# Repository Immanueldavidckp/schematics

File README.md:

# MEWP Telematics Tracker — hardware

CAN-connected GPS/LTE tracker for rental MEWPs (boom/scissor lifts).
Powered from machine batteries with internal Li-ion backup, 2 isolated digital
inputs, 2 low-side outputs, ignition sense, 6-axis IMU, and ≥6 days of local
telemetry buffering.

**Status: milestone 3 complete.** Schematics are drawn and ERC-clean.
Layout has not started and is gated on the open flags below.

| | |
|---|---|
| Target | India · ~₹2,000/unit ex-works at ≥500 pcs · 5-year field life |
| Fab/assembly | JLCPCB (prototypes), Indian EMS later |
| EDA | KiCad 10 |
| Input range | 10.5–100 V DC (80 V packs reach ~96–100 V while charging) |

## Design

| Ref | Part | Function |
|---|---|---|
| U1 | Quectel EC200U-CN | LTE Cat-1 bis + GNSS |
| U2 | Artery AT32F403ACGT7 | MCU, M4 240 MHz, LQFP-48 |
| U3 | QST QMI8658B | 6-axis IMU |
| U4 | SIT1051AT/3 | CAN-FD transceiver |
| U5 | EG Micro EG11752 | 200 V abs-max buck → 5V0 |
| U6 | TI BQ25606 | 1S charger + power path |
| U7 | GD25Q64ESIGR | 8 MB SPI NOR telemetry buffer |
| U8 | TI TXB0104 | 1.8 V ↔ 3.3 V level shift |
| U9 | ME6211C33M5G | 3V3 LDO |

## Layout

```
telematics-tracker.kicad_pro/.kicad_sch/.kicad_pcb   project + root sheet
mcu / storage / io / modem_rf / power .kicad_sch     hierarchical sheets
lib/jlc.kicad_sym, lib/jlc.pretty, lib/jlc.3dshapes  LCSC parts (easyeda2kicad)
tools/schgen.py                                      KiCad S-expression emitter
tools/sheets.py                                      the schematics, as code
tools/checkpins.py                                   netlist-vs-spec guard
docs/                                                see below
erc-*.rpt                                            ERC evidence
```

Sheets are **generated**, not hand-drawn: edit `tools/sheets.py` and run
`python tools/sheets.py`, which rewrites all five sheets plus the root.
Symbol definitions are embedded in each sheet, so they parse without library
resolution. UUIDs are deterministic, so regeneration is diffable.

## Verification

Every change is gated on three checks:

```bash
python tools/sheets.py                                    # regenerate
kicad-cli sch erc  --output erc-full.rpt telematics-tracker.kicad_sch
kicad-cli sch export netlist --format kicadsexpr --output nl.net telematics-tracker.kicad_sch
python tools/checkpins.py nl.net                          # exits non-zero on any mismatch
```

Current: **ERC 0 errors** (14 warnings, each justified in the design log) ·
**48/48** handoff §5 pin-map rows verified against the netlist with far-end
checks · **8/8** DO default-OFF structural assertions.

The netlist guard exists because ERC does not catch everything. It has caught
four real faults that ERC reported only as warnings or not at all: a shorted-out
gate resistor, CANL tied to GND by overlapping stubs, VBAT merged into 3V3, and
a root-sheet wrap-around that shorted three rails.

## Documentation

| File | Contents |
|---|---|
| [design-log.md](design-log.md) | Every decision, deviation and flag, with evidence. Start here. |
| [docs/telematics-handoff.md](docs/telematics-handoff.md) | The governing spec (BOM, pin map, design rules) |
| [docs/f9-review.md](docs/f9-review.md) | EC200U pin-map review table — **sign-off gate** |
| [docs/ec200u-pinmap-extracted.md](docs/ec200u-pinmap-extracted.md) | All 144 pins, VERIFIED / NEEDS-HUMAN |
| [docs/section5-checklist.txt](docs/section5-checklist.txt) | Generated pin-map verification output |
| [docs/firmware-notes.md](docs/firmware-notes.md) | Hardware facts firmware must honour (FW-1…17, BV-1…4) |
| [docs/placement-study.svg](docs/placement-study.svg) | Milestone-4 placement study (provisional outline) |
| [docs/SKILL.md](docs/SKILL.md) | KiCad workflow rules for this project |

## Open flags (blocking layout)

- **F-9** — EC200U symbol came from an EasyEDA entry built around the MobileTek
  L610; its pin numbering contradicts Quectel Table 7 (VBAT_BB 90/91 vs 59/60).
  Only VERIFIED pins are wired; **76 pins are deliberately no-connect**, incl.
  35 probable GND pins. Human sign-off on `docs/f9-review.md` is required before
  layout.
- **F-15** — R80 10 Ω has no load-line solution at the 10.5 V floor at full
  load. Recommend 1 Ω anti-surge (C55348540).
- **F-13** modem bulk caps are X5R 6.3 V on a 4.35 V rail (violates the
  2:1 / X7R rule) · **F-14** six missing test points · **F-12** EG11752 R_IS and
  min-on-time bench items · **F-16** SIM holder locating posts · **F-17** MFF2
  land pattern · **F-5** provisional passive C-numbers.

Nothing here has been fabricated. Re-verify every LCSC C-number on order day.

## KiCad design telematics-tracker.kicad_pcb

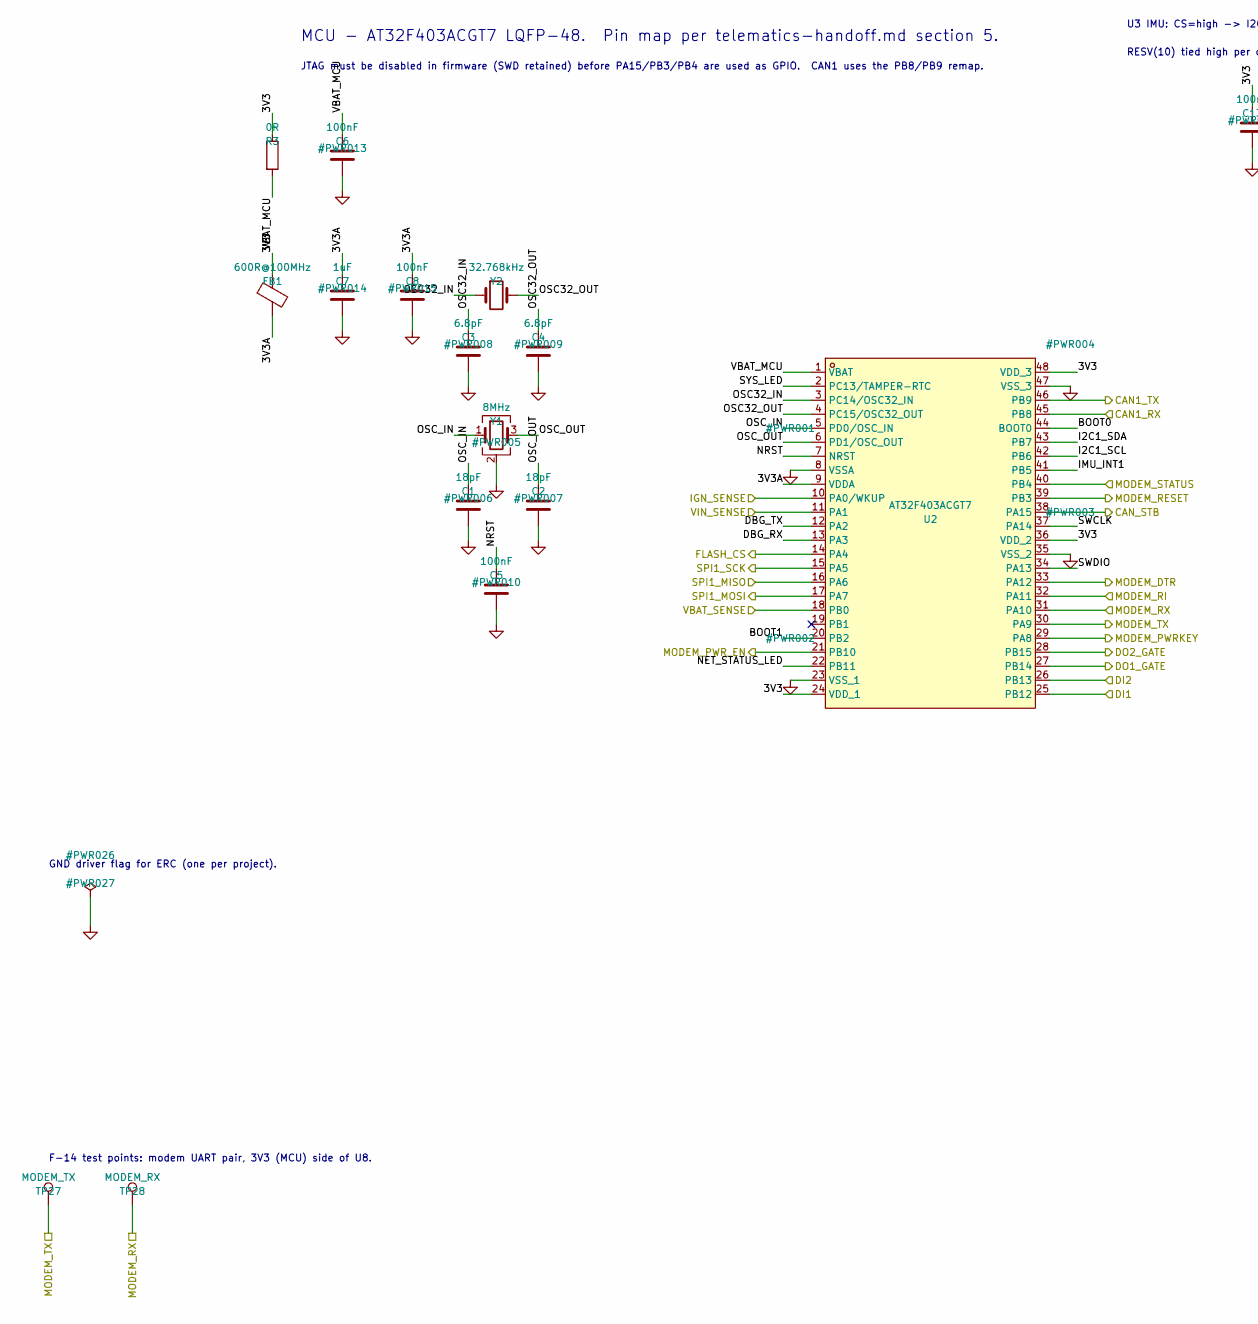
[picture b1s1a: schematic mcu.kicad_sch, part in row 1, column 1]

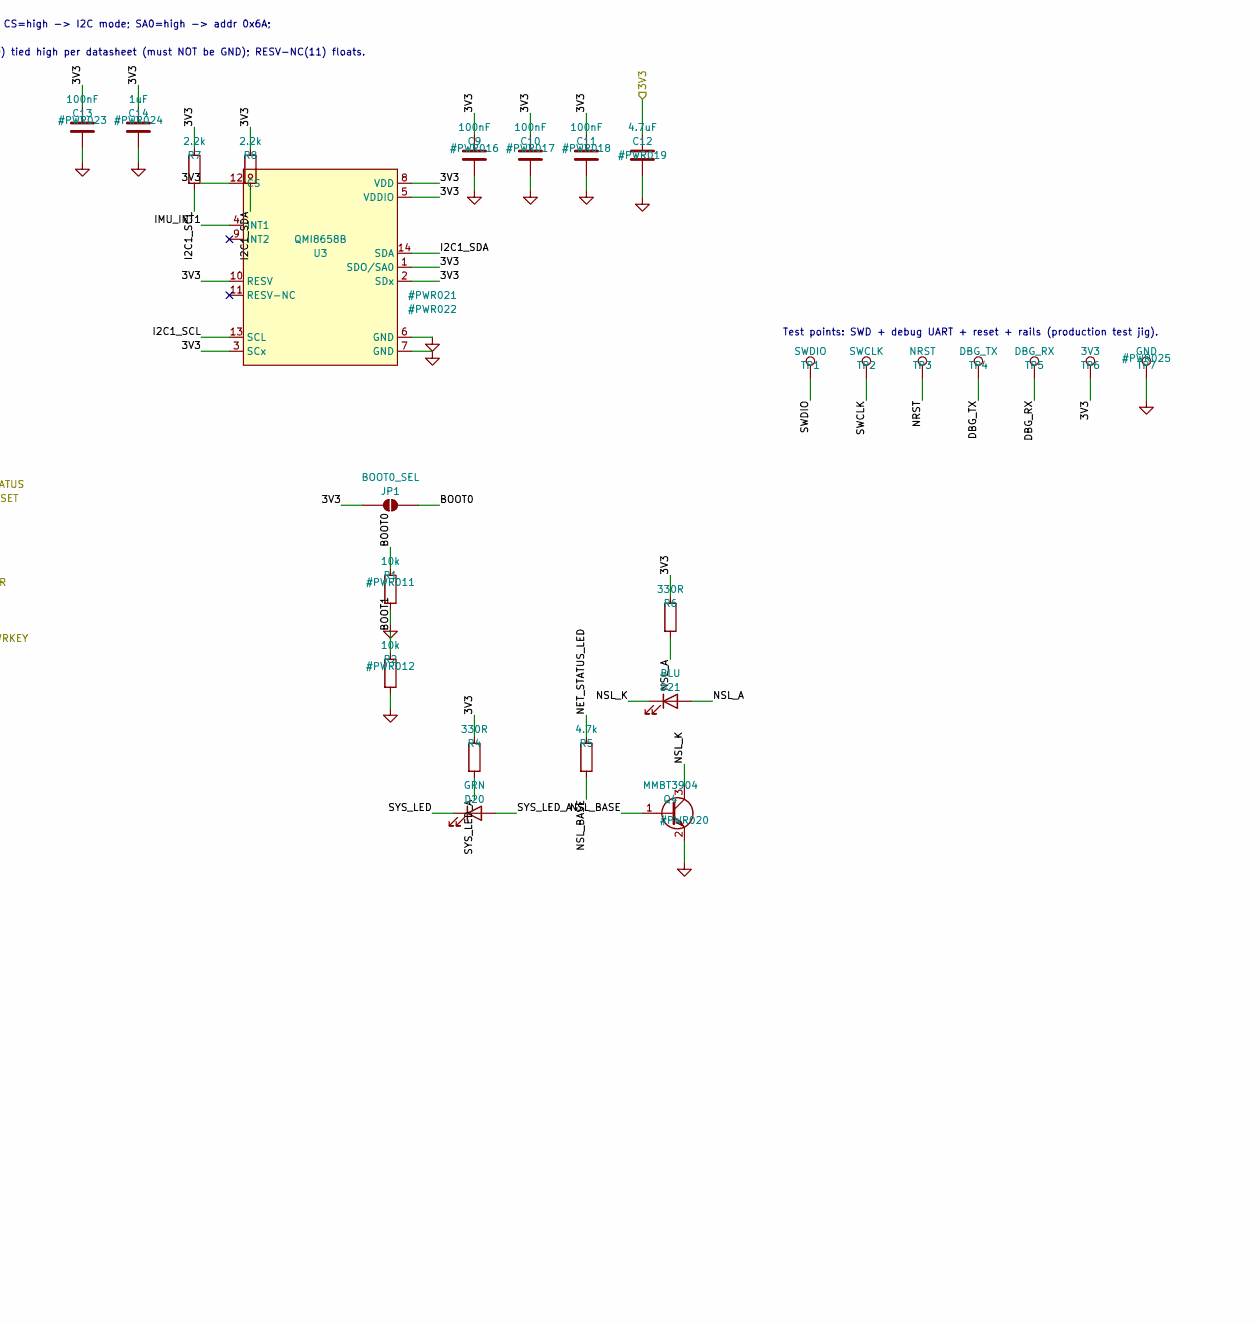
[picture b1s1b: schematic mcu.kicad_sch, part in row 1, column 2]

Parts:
C1, C2: 18pF; C_0603_1608Metric; LCSC C1647
C3, C4: 6.8pF; C_0603_1608Metric; LCSC C318672
C5, C6, C8, C9, C10, C11, C13: 100nF; C_0603_1608Metric; LCSC C14663
C7, C14: 1uF; C_0603_1608Metric; LCSC C106858
C12: 4.7uF; C_0805_2012Metric; LCSC C354262
D20: GRN; LED_0603_1608Metric; LCSC C12624
D21: BLU; LED_0603_1608Metric; LCSC C2288
FB1: 600R@100MHz; L_0805_2012Metric; LCSC C1017
JP1: BOOT0_SEL; SolderJumper-2_P1.3mm_Open_Pad1.0x1.5mm
Q4: MMBT3904; SOT-23; LCSC C20526
R1, R2: 10k; R_0805_2012Metric; LCSC C17414
R3: 0R; R_0805_2012Metric; LCSC C17477
R4, R6: 330R; R_0805_2012Metric; LCSC C17630
R5: 4.7k; R_0805_2012Metric; LCSC C17673
R7, R8: 2.2k; R_0805_2012Metric; LCSC C17520
TP1: SWDIO; TestPoint_Pad_D1.5mm
TP2: SWCLK; TestPoint_Pad_D1.5mm
TP3: NRST; TestPoint_Pad_D1.5mm
TP4: DBG_TX; TestPoint_Pad_D1.5mm
TP5: DBG_RX; TestPoint_Pad_D1.5mm
TP6: 3V3; TestPoint_Pad_D1.5mm
TP7: GND; TestPoint_Pad_D1.5mm
TP27: MODEM_TX; TestPoint_Pad_D1.5mm
TP28: MODEM_RX; TestPoint_Pad_D1.5mm
U2: AT32F403ACGT7; LQFP-48_L7.0-W7.0-P0.50-LS9.0-BL_1; LCSC C55058656
U3: QMI8658B; LGA-14_L3.0-W2.5-P0.50-TL; LCSC C5380158
Y1: 8MHz; Crystal_SMD_3225-4Pin_3.2x2.5mm; LCSC C2682775
Y2: 32.768kHz; Crystal_SMD_3215-2Pin_3.2x1.5mm; LCSC C48615

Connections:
3V3: C9.1, C10.1, C11.1, C12.1, C13.1, C14.1, FB1.1, JP1.1 (A), R3.1, R4.1, R6.1, R7.1, R8.1, TP6.1, U2.24 (VDD_1), U2.36 (VDD_2), U2.48 (VDD_3), U3.1 (SDO/SA0), U3.2 (SDx), U3.3 (SCx), U3.5 (VDDIO), U3.8 (VDD), U3.10 (RESV), U3.12 (CS); also elsewhere on the board
/mcu/3V3A: C7.1, C8.1, FB1.2, U2.9 (VDDA)
/mcu/BOOT0: JP1.2 (B), R1.1, U2.44 (BOOT0)
/mcu/BOOT1: R2.1, U2.20 (PB2)
/mcu/DBG_RX: TP5.1, U2.13 (PA3)
/mcu/DBG_TX: TP4.1, U2.12 (PA2)
/mcu/I2C1_SCL: R7.2, U2.42 (PB6), U3.13 (SCL)
/mcu/I2C1_SDA: R8.2, U2.43 (PB7), U3.14 (SDA)
/mcu/IMU_INT1: U2.41 (PB5), U3.4 (INT1)
/mcu/NET_STATUS_LED: R5.1, U2.22 (PB11)
/mcu/NRST: C5.1, TP3.1, U2.7 (NRST)
/mcu/NSL_A: D21.2 (A), R6.2
/mcu/NSL_BASE: Q4.1 (B), R5.2
/mcu/NSL_K: D21.1 (K), Q4.3 (C)
/mcu/OSC32_IN: C3.1, U2.3 (PC14/OSC32_IN), Y2.1
/mcu/OSC32_OUT: C4.1, U2.4 (PC15/OSC32_OUT), Y2.2
/mcu/OSC_IN: C1.1, U2.5 (PD0/OSC_IN), Y1.1
/mcu/OSC_OUT: C2.1, U2.6 (PD1/OSC_OUT), Y1.3
/mcu/SWCLK: TP2.1, U2.37 (PA14)
/mcu/SWDIO: TP1.1, U2.34 (PA13)
/mcu/SYS_LED: D20.1 (K), U2.2 (PC13/TAMPER-RTC)
/mcu/SYS_LED_A: D20.2 (A), R4.2
/mcu/VBAT_MCU: C6.1, R3.2, U2.1 (VBAT)
CAN1_RX: U2.45 (PB8); also elsewhere on the board
CAN1_TX: U2.46 (PB9); also elsewhere on the board
CAN_STB: U2.38 (PA15); also elsewhere on the board
DI1: U2.25 (PB12); also elsewhere on the board
DI2: U2.26 (PB13); also elsewhere on the board
DO1_GATE: U2.27 (PB14); also elsewhere on the board
DO2_GATE: U2.28 (PB15); also elsewhere on the board
FLASH_CS: U2.14 (PA4); also elsewhere on the board
GND: C1.2, C2.2, C3.2, C4.2, C5.2, C6.2, C7.2, C8.2, C9.2, C10.2, C11.2, C12.2, C13.2, C14.2, Q4.2 (E), R1.2, R2.2, TP7.1, U2.8 (VSSA), U2.23 (VSS_1), U2.35 (VSS_2), U2.47 (VSS_3), U3.6 (GND), U3.7 (GND), Y1.2 (G), Y1.4 (G); also elsewhere on the board
IGN_SENSE: U2.10 (PA0/WKUP)
MODEM_DTR: U2.33 (PA12); also elsewhere on the board
MODEM_PWRKEY: U2.29 (PA8); also elsewhere on the board
MODEM_PWR_EN: U2.21 (PB10); also elsewhere on the board
MODEM_RESET: U2.39 (PB3); also elsewhere on the board
MODEM_RI: U2.32 (PA11); also elsewhere on the board
MODEM_RX: TP28.1, U2.31 (PA10); also elsewhere on the board
MODEM_STATUS: U2.40 (PB4); also elsewhere on the board
MODEM_TX: TP27.1, U2.30 (PA9); also elsewhere on the board
SPI1_MISO: U2.16 (PA6); also elsewhere on the board
SPI1_MOSI: U2.17 (PA7); also elsewhere on the board
SPI1_SCK: U2.15 (PA5); also elsewhere on the board
VBAT_SENSE: U2.18 (PB0)
VIN_SENSE: U2.11 (PA1)

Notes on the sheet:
MCU - AT32F403ACGT7 LQFP-48. Pin map per telematics-handoff.md section 5.
JTAG must be disabled in firmware (SWD retained) before PA15/PB3/PB4 are used as GPIO. CAN1 uses the PB8/PB9 remap.
U3 IMU: CS=high -> I2C mode; SA0=high -> addr 0x6A;
RESV(10) tied high per datasheet (must NOT be GND); RESV-NC(11) floats.
Test points: SWD + debug UART + reset + rails (production test jig).
F-14 test points: modem UART pair, 3V3 (MCU) side of U8.
GND driver flag for ERC (one per project).

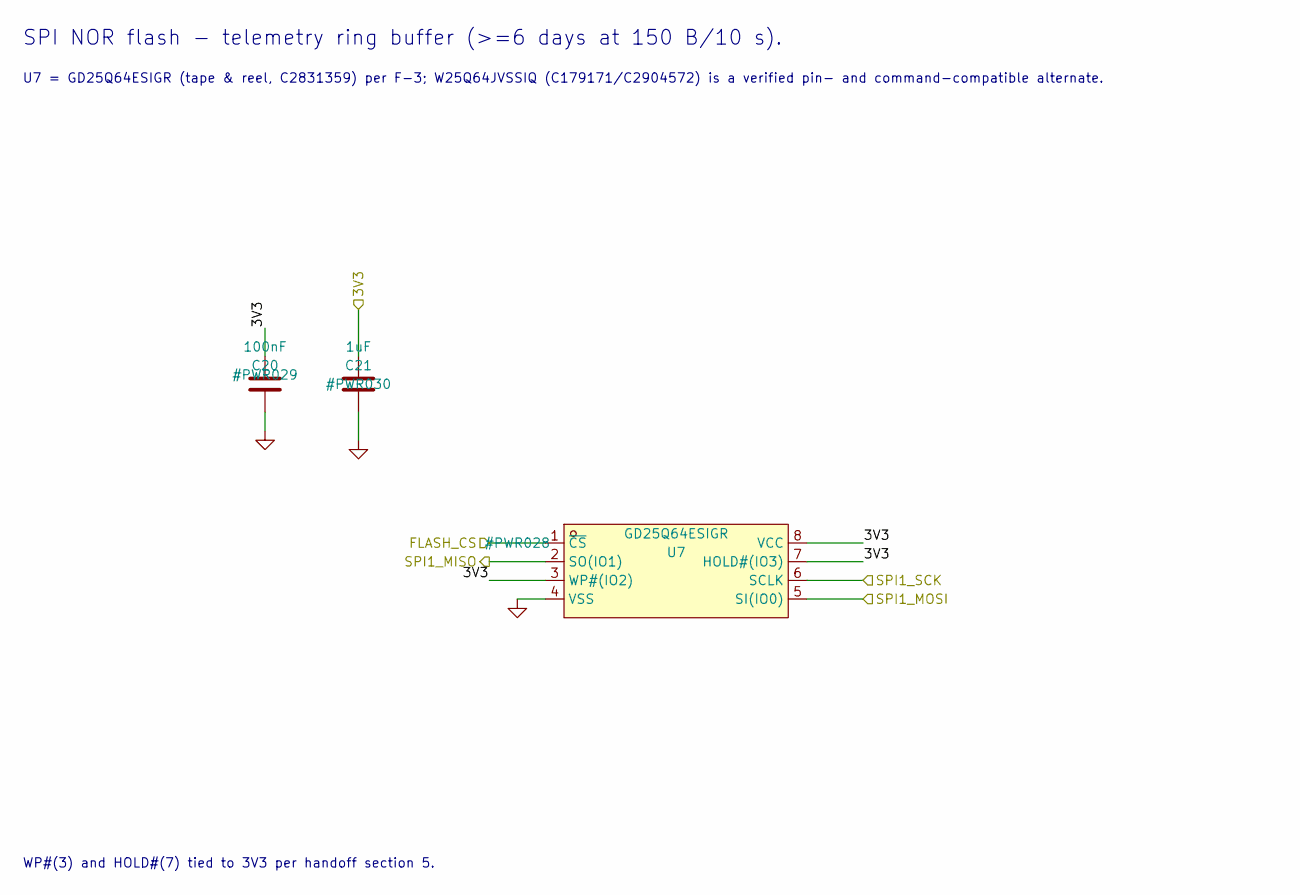
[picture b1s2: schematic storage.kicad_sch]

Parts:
C20: 100nF; C_0603_1608Metric; LCSC C14663
C21: 1uF; C_0603_1608Metric; LCSC C106858
U7: GD25Q64ESIGR; SOP-8_L5.3-W5.3-P1.27-LS8.0-BL; LCSC C2831359

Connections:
3V3: C20.1, C21.1, U7.3 (WP#(IO2)), U7.7 (HOLD#(IO3)), U7.8 (VCC); also elsewhere on the board
FLASH_CS: U7.1 (~CS); also elsewhere on the board
GND: C20.2, C21.2, U7.4 (VSS); also elsewhere on the board
SPI1_MISO: U7.2 (SO(IO1)); also elsewhere on the board
SPI1_MOSI: U7.5 (SI(IO0)); also elsewhere on the board
SPI1_SCK: U7.6 (SCLK); also elsewhere on the board

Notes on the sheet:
SPI NOR flash - telemetry ring buffer (>=6 days at 150 B/10 s).
U7 = GD25Q64ESIGR (tape & reel, C2831359) per F-3; W25Q64JVSSIQ (C179171/C2904572) is a verified pin- and command-compatible alternate.
WP#(3) and HOLD#(7) tied to 3V3 per handoff section 5.

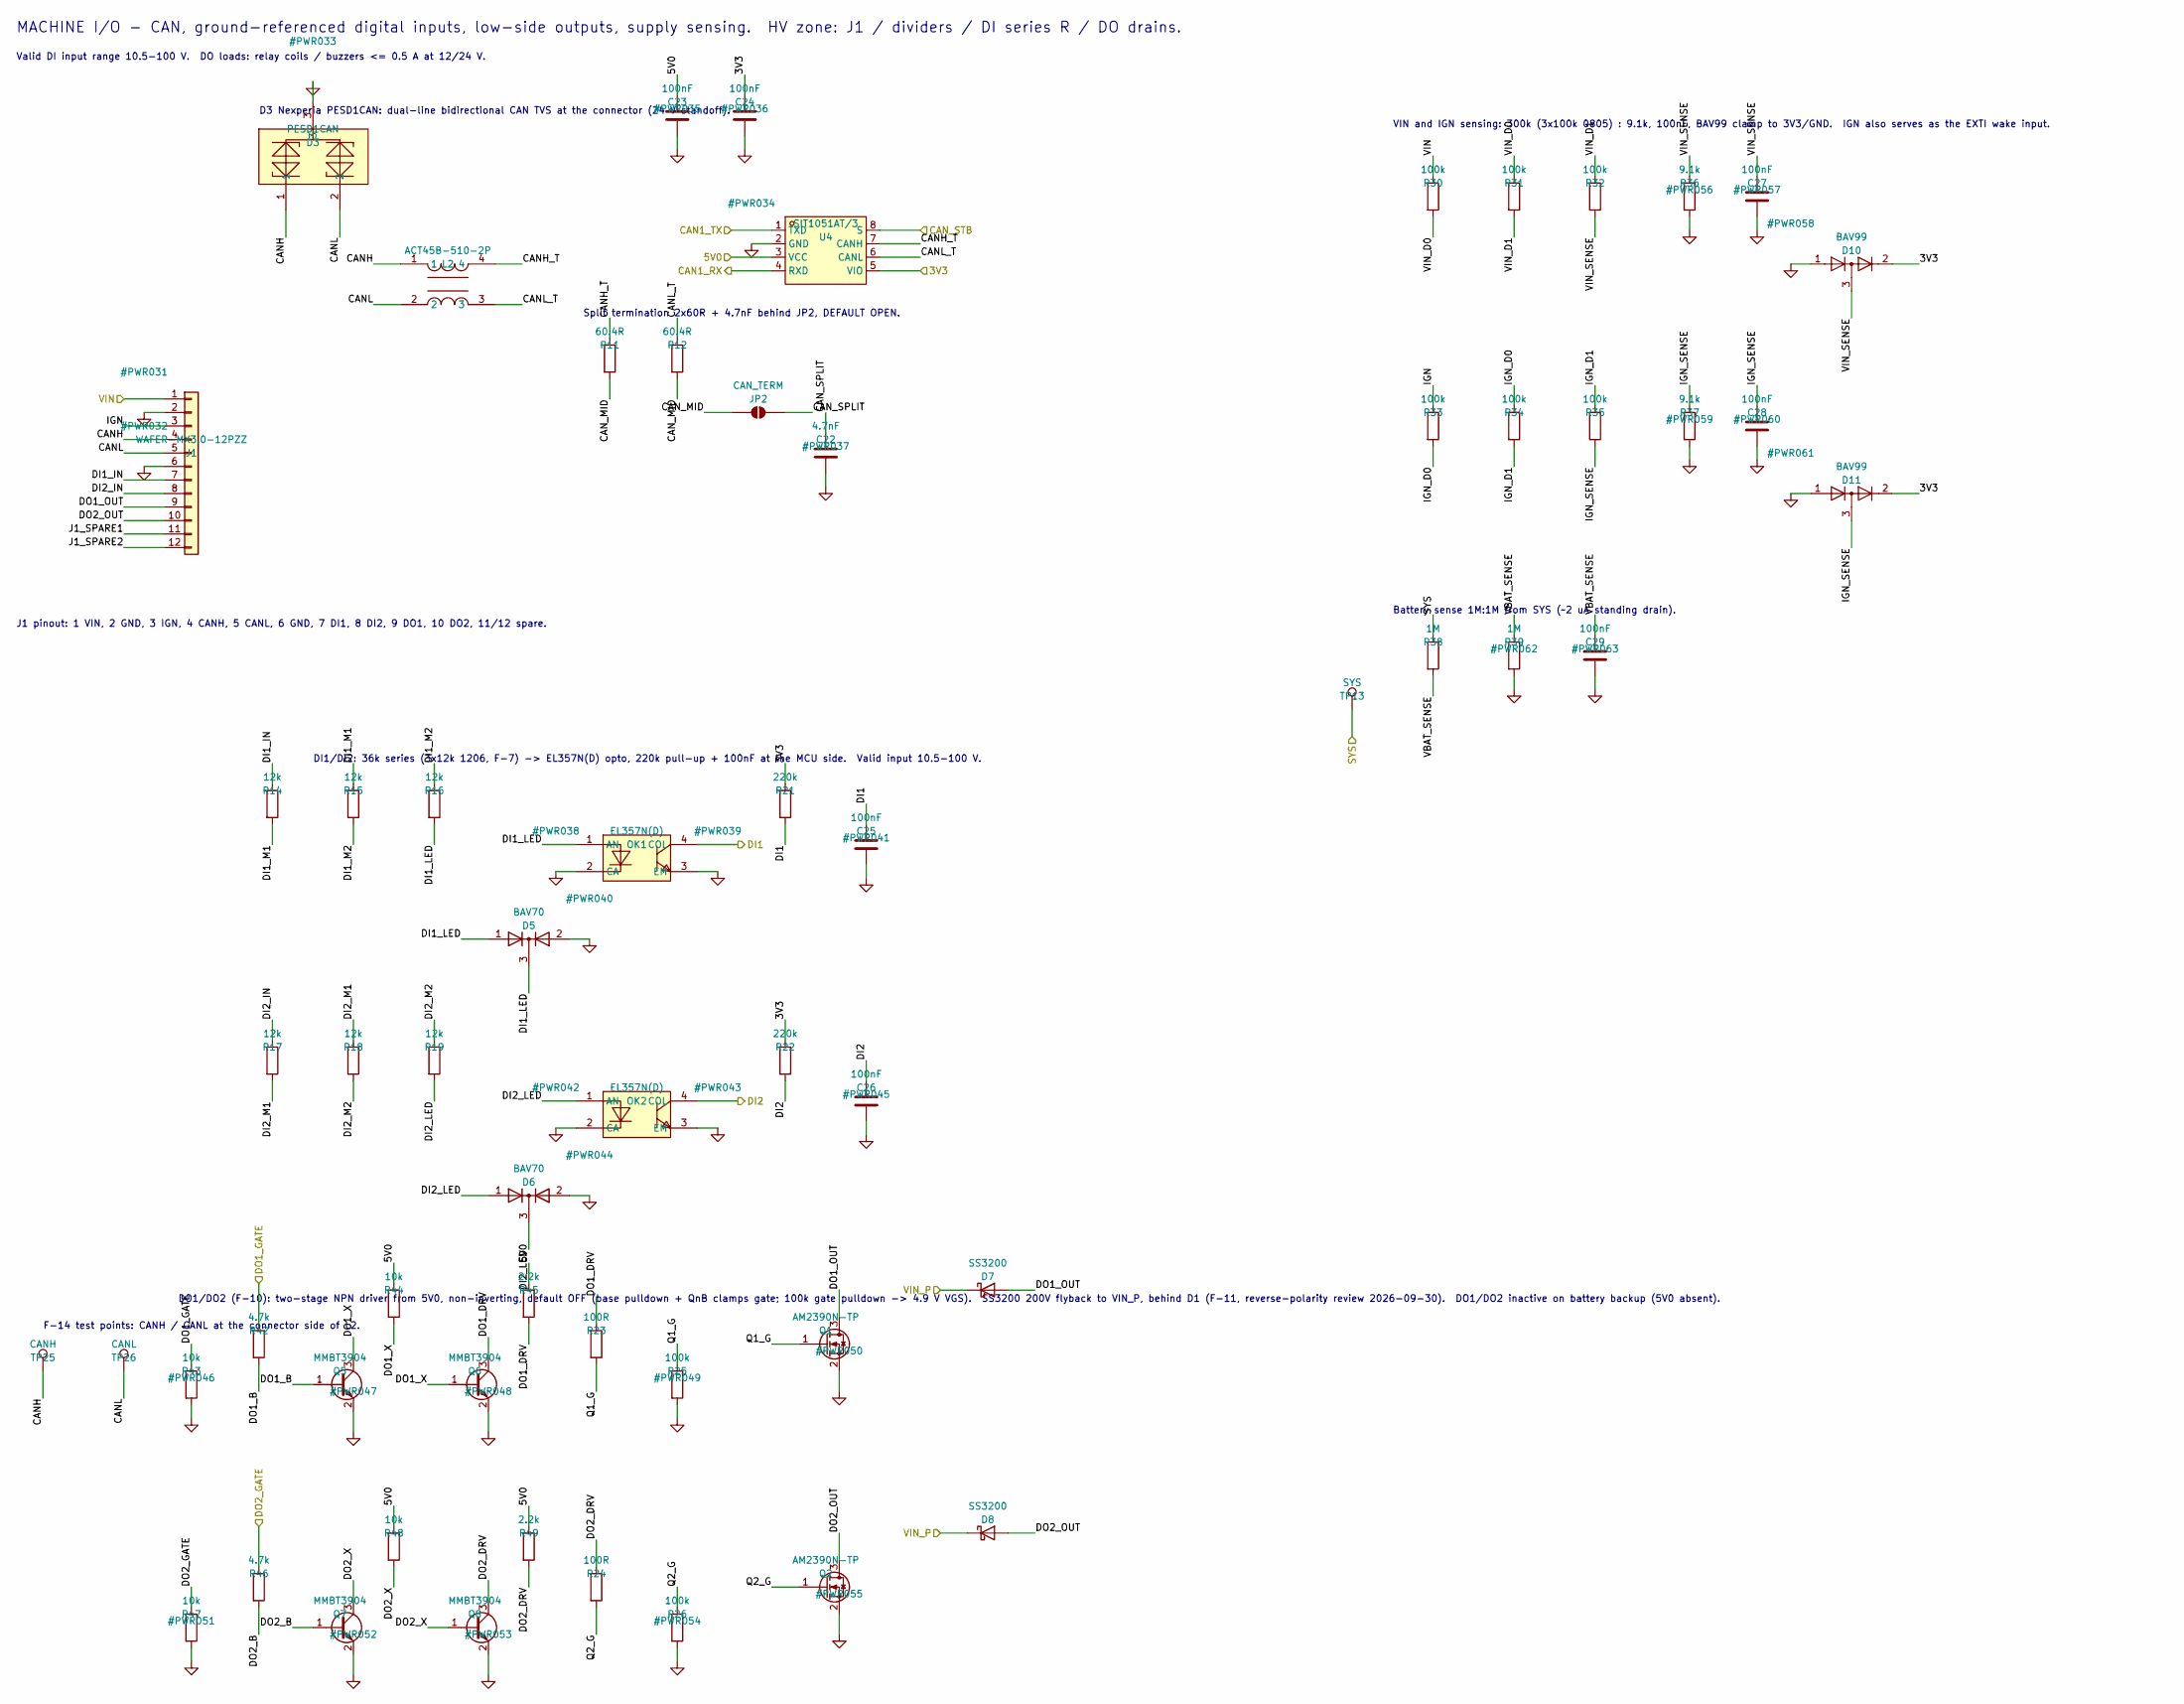
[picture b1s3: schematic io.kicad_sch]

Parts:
C22: 4.7nF; C_0603_1608Metric; LCSC C1621
C23, C24, C25, C26, C27, C28, C29: 100nF; C_0603_1608Metric; LCSC C14663
D3: PESD1CAN; SOT-23_L2.9-W1.3-P1.90-LS2.4-BR; LCSC C15771
D5, D6: BAV70; SOT-23; LCSC C2501
D7, D8: SS3200; D_SMA; LCSC C65001
D10, D11: BAV99; SOT-23; LCSC C2500
J1: WAFER-MX3.0-12PZZ; XUNPU_MX3.0-12PZZ_2x06_P3.00mm_Vertical; LCSC C7588012
JP2: CAN_TERM; SolderJumper-2_P1.3mm_Open_Pad1.0x1.5mm
L2: ACT45B-510-2P; IND-SMD_4P-L4.5-W3.2-TL; LCSC C76584
OK1, OK2: EL357N(D); OPTO-SMD-4_L4.4-W4.1-P2.54-LS7.0-BL; LCSC C359074
Q1, Q2: AM2390N-TP; SOT-23-3_L2.9-W1.3-P1.90-LS2.4-BR; LCSC C51886143
Q5, Q6, Q7, Q8: MMBT3904; SOT-23; LCSC C20526
R11, R12: 60.4R; R_0805_2012Metric; LCSC C228935
R14, R15, R16, R17, R18, R19: 12k; R_1206_3216Metric; LCSC C17912
R21, R22: 220k; R_0805_2012Metric; LCSC C17556
R23, R24: 100R; R_0805_2012Metric; LCSC C17408
R25, R26, R30, R31, R32, R33, R34, R35: 100k; R_0805_2012Metric; LCSC C149504
R36, R37: 9.1k; R_0805_2012Metric; LCSC C17855
R38, R39: 1M; R_0805_2012Metric; LCSC C17514
R42, R46: 4.7k; R_0805_2012Metric; LCSC C17673
R43, R44, R47, R48: 10k; R_0805_2012Metric; LCSC C17414
R45, R49: 2.2k; R_0805_2012Metric; LCSC C17520
TP13: SYS; TestPoint_Pad_D1.5mm
TP25: CANH; TestPoint_Pad_D1.5mm
TP26: CANL; TestPoint_Pad_D1.5mm
U4: SIT1051AT/3; SOP-8_L4.9-W3.9-P1.27-LS6.0-BL; LCSC C5382551

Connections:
3V3: C24.1, D10.2 (A), D11.2 (A), R21.1, R22.1, U4.5 (VIO); also elsewhere on the board
5V0: C23.1, R44.1, R45.1, R48.1, R49.1, U4.3 (VCC); also elsewhere on the board
/io/CANH: D3.1, J1.4, L2.1, TP25.1
/io/CANH_T: L2.4, R11.1, U4.7 (CANH)
/io/CANL: D3.2, J1.5, L2.2, TP26.1
/io/CANL_T: L2.3, R12.1, U4.6 (CANL)
/io/CAN_MID: JP2.1 (A), R11.2, R12.2
/io/CAN_SPLIT: C22.1, JP2.2 (B)
/io/DI1_IN: J1.7, R14.1
/io/DI1_LED: D5.1 (A), D5.3 (K), OK1.1 (AN), R16.2
/io/DI1_M1: R14.2, R15.1
/io/DI1_M2: R15.2, R16.1
/io/DI2_IN: J1.8, R17.1
/io/DI2_LED: D6.1 (A), D6.3 (K), OK2.1 (AN), R19.2
/io/DI2_M1: R17.2, R18.1
/io/DI2_M2: R18.2, R19.1
/io/DO1_B: Q5.1 (B), R42.2
/io/DO1_DRV: Q6.3 (C), R23.1, R45.2
/io/DO1_OUT: D7.2 (A), J1.9, Q1.3 (D)
/io/DO1_X: Q5.3 (C), Q6.1 (B), R44.2
/io/DO2_B: Q7.1 (B), R46.2
/io/DO2_DRV: Q8.3 (C), R24.1, R49.2
/io/DO2_OUT: D8.2 (A), J1.10, Q2.3 (D)
/io/DO2_X: Q7.3 (C), Q8.1 (B), R48.2
/io/IGN: J1.3, R33.1
/io/IGN_D0: R33.2, R34.1
/io/IGN_D1: R34.2, R35.1
/io/IGN_SENSE: C28.1, D11.3 (K), R35.2, R37.1
/io/J1_SPARE1: J1.11
/io/J1_SPARE2: J1.12
/io/Q1_G: Q1.1 (G), R23.2, R25.1
/io/Q2_G: Q2.1 (G), R24.2, R26.1
/io/VBAT_SENSE: C29.1, R38.2, R39.1
/io/VIN_D0: R30.2, R31.1
/io/VIN_D1: R31.2, R32.1
/io/VIN_SENSE: C27.1, D10.3 (K), R32.2, R36.1
CAN1_RX: U4.4 (RXD); also elsewhere on the board
CAN1_TX: U4.1 (TXD); also elsewhere on the board
CAN_STB: U4.8 (S); also elsewhere on the board
DI1: C25.1, OK1.4 (COL), R21.2; also elsewhere on the board
DI2: C26.1, OK2.4 (COL), R22.2; also elsewhere on the board
DO1_GATE: R42.1, R43.1; also elsewhere on the board
DO2_GATE: R46.1, R47.1; also elsewhere on the board
GND: C22.2, C23.2, C24.2, C25.2, C26.2, C27.2, C28.2, C29.2, D3.3, D5.2 (A), D6.2 (A), D10.1 (K), D11.1 (K), J1.2, J1.6, OK1.2 (CA), OK1.3 (EM), OK2.2 (CA), OK2.3 (EM), Q1.2 (S), Q2.2 (S), Q5.2 (E), Q6.2 (E), Q7.2 (E), Q8.2 (E), R25.2, R26.2, R36.2, R37.2, R39.2, R43.2, R47.2, U4.2 (GND); also elsewhere on the board
SYS: R38.1, TP13.1; also elsewhere on the board
VIN: J1.1, R30.1; also elsewhere on the board
VIN_P: D7.1 (K), D8.1 (K); also elsewhere on the board

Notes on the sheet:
MACHINE I/O - CAN, ground-referenced digital inputs, low-side outputs, supply sensing. HV zone: J1 / dividers / DI series R / DO drains.
Valid DI input range 10.5-100 V. DO loads: relay coils / buzzers <= 0.5 A at 12/24 V.
J1 pinout: 1 VIN, 2 GND, 3 IGN, 4 CANH, 5 CANL, 6 GND, 7 DI1, 8 DI2, 9 DO1, 10 DO2, 11/12 spare.
D3 Nexperia PESD1CAN: dual-line bidirectional CAN TVS at the connector (24 V standoff).
F-14 test points: CANH / CANL at the connector side of L2.
Split termination 2x60R + 4.7nF behind JP2, DEFAULT OPEN.
DI1/DI2: 36k series (3x12k 1206, F-7) -> EL357N(D) opto, 220k pull-up + 100nF at the MCU side. Valid input 10.5-100 V.
DO1/DO2 (F-10): two-stage NPN driver from 5V0, non-inverting, default OFF (base pulldown + QnB clamps gate; 100k gate pulldown -> 4.9 V VGS). SS3200 200V flyback to VIN_P, behind D1 (F-11, reverse-polarity review 2026-09-30). DO1/DO2 inactive on battery backup (5V0 absent).
VIN and IGN sensing: 300k (3x100k 0805) : 9.1k, 100nF, BAV99 clamp to 3V3/GND. IGN also serves as the EXTI wake input.
Battery sense 1M:1M from SYS (~2 uA standing drain).
